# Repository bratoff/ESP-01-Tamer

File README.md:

# ESP-01-Tamer
Breadboard-friendly breakout, level shift and programming adapter for ESP-01 ESP8266 module.

This little board makes it super easy to use the ESP-8266 ESP-01 board in the Arduino environment.  

The following features are provided:  
- CH340G based USB serial interface  
- Auto control of RST/IO0 for downloading (uses DTR and RTS)  
- Onboard 3.3v regulator  
- Bidirectional 5v/3.3v logic level conversion on Rx, Tx, IO0, IO2  
- Breadboard-friendly breakout of all essential pins  

There are two versions of this board:  
ESP-01_Tamer   - all above features, with a USB A male connector to host  
ESP-01_Tamer-u - all the same features, but with a micro USB female conneector to host  

Common parts list:  
R1-R9 -   10K 0805 size  
R10,R11 - 470 ohm 0805 size  
R12,R13 - 10K 0805 size  
Y1 - 12mhz SMD-3 ceramic resonator  
IC1 - LD117AS33TR SOT223 3.3v 3-terminal regulator  
IC2 - CH340G USB to serial interface  
D1 - B5819W-TP SOD123 Schottky diode  
C1,C4 - 100nf 0805 size  
C2,C3 - 10uf 0805 size  
Q1-Q4 - 2N7002 SOT23  
Q5,Q6 - S8050 SOT23  
JP1 - 2x4 0.1" thru-hole female header  
JP2,JP3 - 1x4 0.1" thru-hole male header  

USB-A version only:  
JP4 - USB A male thru-hole PCB connector  

Micro-USB version only:  
JP4 - 1x1 0.1" thru-hole male header (in case you need the micro USB ID pin)  
J1 - Hirose  ZX62D-B-5PA8 micro USB female surface mount connector  

PC boards are available on OSHpark:  
USB-A:  <https://oshpark.com/shared_projects/sAVimhVZ>  
microUSB: <https://oshpark.com/shared_projects/1ui7zgvW>

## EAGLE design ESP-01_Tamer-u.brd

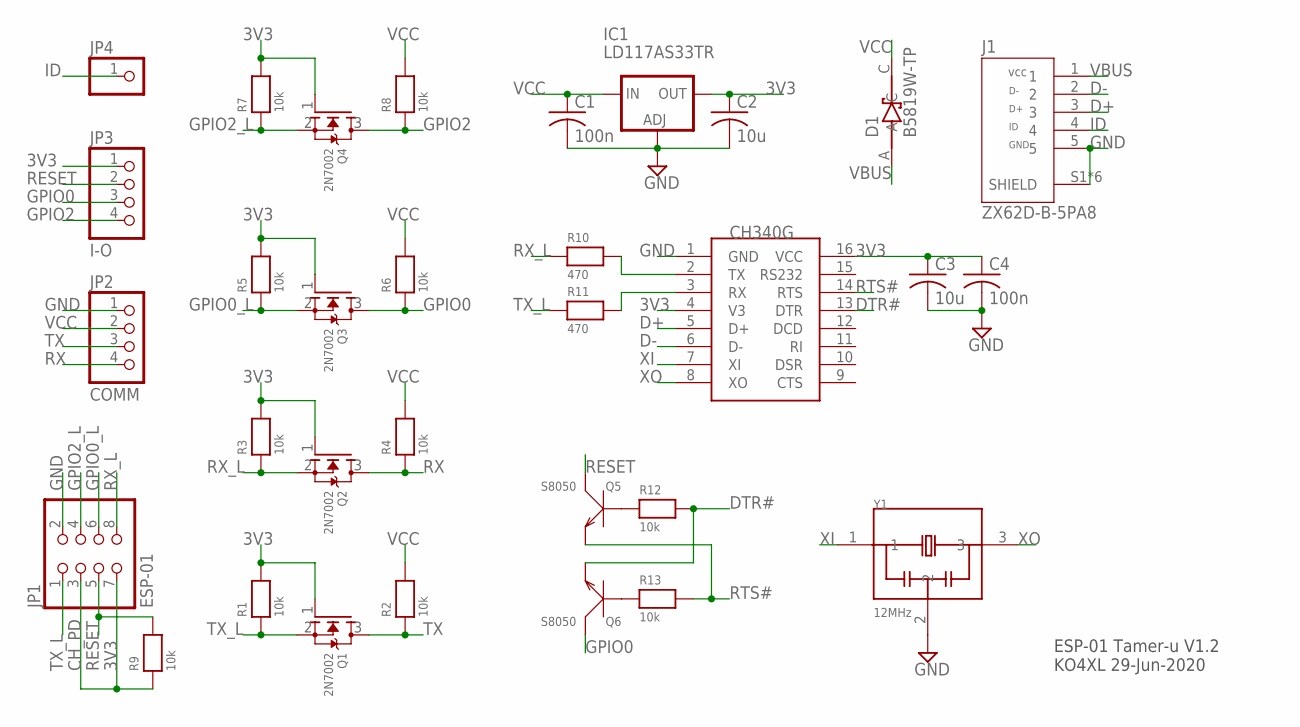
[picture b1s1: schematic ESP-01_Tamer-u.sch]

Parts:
C1, C4: 100n; C0805K
C2, C3: 10u; C0805K
D1: B5819W-TP; SOD3716X135N
IC1: LD117AS33TR; SOT223
IC2: CH340G; SOIC16
J1: ZX62D-B-5PA8; HIROSE_ZX62D-B-5PA8
JP1: ESP-01; 2X04
JP2: COMM; 1X04_ROUND
JP3: I-O; 1X04_ROUND
JP4: HEADER-1X1ROUND; 1X01_ROUND
Q1, Q2, Q3, Q4: 2N7002; SOT23-WIDE
Q5, Q6: S8050; SOT-23
R1, R2, R3, R4, R5, R6, R7, R8, R9, R12, R13: 10k; 0805_NOTHERMALS
R10, R11: 470; 0805_NOTHERMALS
Y1: 12MHz; OSC_CSTCE8M00G55-R0

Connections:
3V3: C2.1, C3.1, C4.1, IC1.4 (OUT), IC2.4 (V3), IC2.16 (VCC), JP1.3, JP1.7, JP3.1, Q1.1 (G), Q2.1 (G), Q3.1 (G), Q4.1 (G), R1.2, R3.2, R5.2, R7.2, R9.1
D+: IC2.5 (D+), J1.3
D-: IC2.6 (D-), J1.2
DTR#: IC2.13 (DTR), Q6.2 (E), R12.2
GND: C1.2, C2.2, C3.2, C4.2, IC1.1 (ADJ), IC2.1 (GND), J1.5, J1.S1 (SHIELD), J1.S2 (SHIELD), J1.S3 (SHIELD), J1.S4 (SHIELD), J1.S5 (SHIELD), J1.S6 (SHIELD), JP1.2, JP2.1, Y1.2
GPIO0: JP3.3, Q3.3 (D), Q6.3 (C), R6.1
GPIO0_L: JP1.6, Q3.2 (S), R5.1
GPIO2: JP3.4, Q4.3 (D), R8.1
GPIO2_L: JP1.4, Q4.2 (S), R7.1
ID: J1.4, JP4.1
unnamed: Q5.1 (B), R12.1
unnamed: Q6.1 (B), R13.1
unnamed: IC2.2 (TX), R10.2
unnamed: IC2.3 (RX), R11.2
RESET: JP1.5, JP3.2, Q5.3 (C), R9.2
RTS#: IC2.14 (RTS), Q5.2 (E), R13.2
RX: JP2.4, Q2.3 (D), R4.1
RX_L: JP1.8, Q2.2 (S), R3.1, R10.1
TX: JP2.3, Q1.3 (D), R2.1
TX_L: JP1.1, Q1.2 (S), R1.1, R11.1
VBUS: D1.A, J1.1
VCC: C1.1, D1.C, IC1.3 (IN), JP2.2, R2.2, R4.2, R6.2, R8.2
XI: IC2.7 (XI), Y1.1
XO: IC2.8 (XO), Y1.3

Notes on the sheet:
CH_PD
ESP-01 Tamer-u V1.2 KO4XL 29-Jun-2020

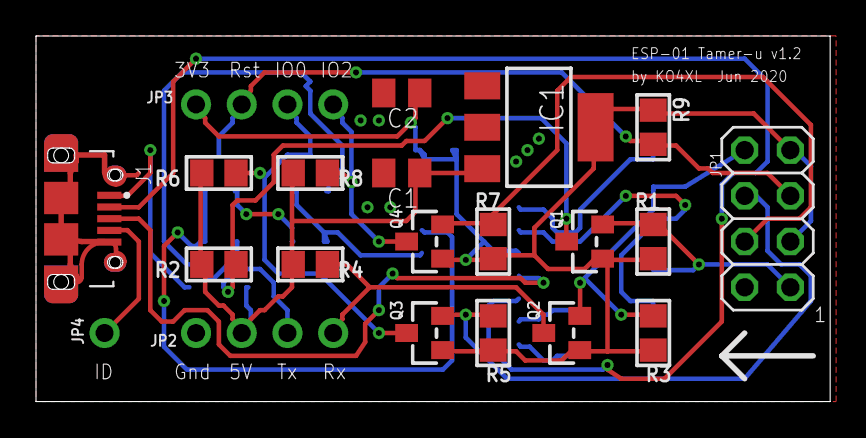
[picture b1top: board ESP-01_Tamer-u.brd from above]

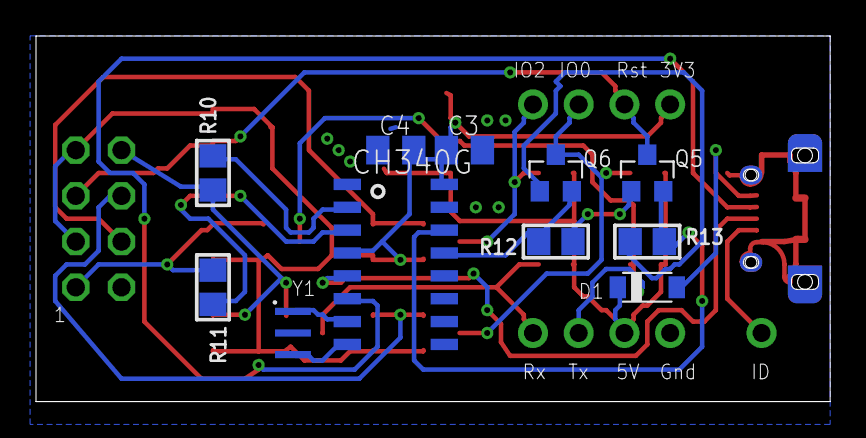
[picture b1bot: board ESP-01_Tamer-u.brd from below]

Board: 2 copper layers, 44.1 x 20.3 mm, 32 parts (11 on the bottom side), 24 nets.

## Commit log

2020-07-31 Commit microUSB version
    Add "u" files, update readme

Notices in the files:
parts and their libraries:
microbuilder: This work is placed in the public domain, and may be freely used for commercial and non-commercial work with the following conditions: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
